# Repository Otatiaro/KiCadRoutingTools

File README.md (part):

# KiCad Routing Tools

A fast Rust-accelerated A* autorouter for KiCad PCB files. Compatible with **KiCad 9 and KiCad 10**. Available as both a **KiCad Plugin** with full GUI and a **Command-Line Interface** for scripting and automation.

📊 **[Project metrics](https://drandyhaas.github.io/KiCadRoutingTools/metrics/)** — installs, downloads and traffic, updated daily.

<p align="center">
  
  <br>
  Free and MIT-licensed. Donations cover the ~$500/month of cloud compute and AI development behind it.
  <br>
  Also via <a href="https://github.com/sponsors/drandyhaas">GitHub Sponsors</a> or <a href="https://www.paypal.me/DrAndyHaas">PayPal</a> — see <a href="#support">Support</a>.
</p>

## Contents

- [Support](#support) — donate via Ko-fi, GitHub Sponsors or PayPal
- [Features](#features)
- [Quick Start](#quick-start)
- [KiCad Plugin](#kicad-plugin) — GUI, the **AI Drive** tab (routing and placement), installation
- [Command-Line Interface](#command-line-interface) — routing, planes, verification
- [Documentation](#documentation) — full guide for every feature
- [Project Structure](#project-structure) & [Module Overview](#module-overview)
- [Performance](#performance)
- [Command Reference](#command-reference) — options per tool (full list: `--help` / [configuration.md](docs/configuration.md))
- [Project metrics](https://drandyhaas.github.io/KiCadRoutingTools/metrics/) — installs, downloads and traffic
- [Requirements](#requirements) · [Limitations](#limitations) · [Contributing](#contributing) · [License](#license)

## Support

KiCadRoutingTools is free and MIT-licensed, and it stays that way — there is no
paid tier, no feature held back, and nothing in this repository is paywalled.

Donations go to what it costs to build and maintain it: about **$500/month** of
cloud computing and AI-assisted development.

The compute is not incidental. Every change to the router is A/B-tested by
replaying a corpus of real open-source boards on rented cores and grading each
one for DRC violations and unconnected nets, and the ~770-file test suite fans
out the same way. It is what stops a change that helps one board from quietly
breaking ten others.

- **[☕ Donate on Ko-fi](https://ko-fi.com/drandyhaas)** — card or PayPal, no account needed.
- **[GitHub Sponsors](https://github.com/sponsors/drandyhaas)** — one-time or monthly, billed with any other projects you sponsor.
- Prefer PayPal directly? **[paypal.me/DrAndyHaas](https://www.paypal.me/DrAndyHaas)** (the sender needs a PayPal account).

A donation buys no priority support and unlocks no features. If you would rather
contribute something worth more than money, route one of your own boards and file
an issue for whatever breaks — see [Contributing](#contributing).

## Features

Fast, grid-based A\* routing with a native Rust core (~10× faster than pure Python): octilinear (H/V/45°) multi-layer routing with automatic vias, and batch routing with incremental obstacle caching. Highlights below link to the full deep-dive docs.

**Core routing**
- Rust-accelerated A\* pathfinding, multi-layer with automatic via insertion
- [Rip-up and reroute](docs/rip-up-reroute.md) — progressive N+1 blocker analysis, ripped-corridor avoidance
- [Net ordering strategies](docs/net-ordering.md) — MPS (crossing-aware), inside-out, original, or bus-first, with MPS layer swaps
- Stub layer switching, vertical track alignment, turn-cost straightening
- Board-edge (Edge.Cuts arcs/cutouts), keep-out rule areas, and auto BGA exclusion zones — see [Configuration](docs/configuration.md)
- Direction-aware stub / BGA / track [proximity penalties](docs/configuration.md)

**Differential pairs** — see [Differential Pairs](docs/differential-pairs.md)
- Pose-based A\* with a Dubins heuristic and adaptive setback angles for orientation-aware centerlines
- Bare-pad, multi-point (3+ terminals), and hybrid (coupled middle + single-ended legs) routing
- Automatic polarity resolution (opt-in pad swaps), U-turn prevention, GND return-via placement
- Electrically-short legs auto-defer to single-ended; per-layer [impedance-controlled](docs/differential-pairs.md) widths

**Power & planes** — see [Plane Routing](docs/route-plane.md) and [Power Nets](docs/power-nets.md)
- [Wider power-net routing](docs/power-nets.md) with automatic neck-down at fine-pitch pads
- Plane pours (pads are welded by the route step, #562) and plane layers several nets share (split round spines routed on the layer) with resistance / max-current reporting
- Disconnected-plane-region repair (region joins + pad taps) and GND return-via placement

**Signal integrity**
- [Length matching](docs/length-matching.md) — trombone meanders, auto DQ/DQS grouping, via-barrel aware
- [Time matching](docs/length-matching.md#time-matching) — propagation delay, microstrip vs stripline
- [Bus routing](docs/bus-routing.md), plus [guide corridors and keep-out zones](docs/configuration.md) drawn on a User layer

**Placement, fanout & optimization**
- [Placement by function](py_placer/placement/README.md): parts sorted into functional groups, one objective annealed (`place_simple.py`) over 12 seeds (6 started scattered, 6 with each group gathered), and a fast route (`route.py --quick 2`) of the 6 the objective rates best to keep the best (`/plan-pcb-placement`)
- [The design brief](docs/design-brief.md) — state what the board is FOR, in a sibling the toolchain reads: which connectors are user-facing, which edge each belongs on and where along it
- [Parts under other parts](docs/floorplan-intent.md#covers-and-heights-what-stands-over-the-board) — part heights read off the 3D models, so a low part may stand under a module or shield can where it fits; a card in its socket (M.2) or a module on a stacking connector is declared in the brief and moves with its connector, admitting only parts known to fit under it
- [Floorplan intent, graded](docs/floorplan-intent.md) — declare where parts belong and check the board against it, so "the render looks fine" stops being a verdict
- BGA / QFN fanout with decoupling-cap placement cleanup, Hungarian target-swap, and schematic sync

**Cleanup & verification** — see [Utilities](docs/utilities.md)
- Post-route copper cleanup reconciled against the connectivity model (no orphaned or ripped-and-not-restored copper), with gap-snap connectors
- **KiCad-oracle reconnect** — routes the exact links KiCad's own DRC reports as unconnected
- Checkers for DRC, connectivity, orphan stubs, copper hygiene (`check_weird.py`), and pad geometry

**Interfaces**
- Full [KiCad plugin GUI](#kicad-plugin) (KiCad 9 & 10) and a scriptable [CLI](#command-line-interface)
- [AI assistance](docs/claude-skills.md) — an **AI Drive** tab that plans an entire routing workflow or places a board by function, per-field "Ask AI" helpers, and datasheet-driven power / high-speed / diff-pair analysis
- [Board rendering](docs/utilities.md#board-renderer-route_renderpy) — fast geometry PNG renderer (`route_render.py`), placement stills (`render_placement.py`), a board's power components (`render_power.py`), and movies of a routing run (`route_movie.py`, made for every stress run) and of a placement, or the placement skill's whole flow through to the full route (`place_movie.py`)
- [Routing plans as files](docs/claude-skills.md#plans-from-the-command-line) — save/load a whole routing chain as JSON: build one from a recorded command chain (`make_plan.py`), run it headless through the real plugin (`run_plan.py`), or load it in the GUI

## Quick Start

### 1. Get the Code

```bash
# Clone with git
git clone https://github.com/drandyhaas/KiCadRoutingTools.git
cd KiCadRoutingTools
```

Or [download the ZIP](https://github.com/drandyhaas/KiCadRoutingTools/archive/refs/heads/main.zip) and extract it.

Commands here use `python3`. On Windows, use `py -3` (or `python`) if `python3` is not found.

### 2. Install the Rust Router

```bash
python3 build_router.py
```

By default this downloads a prebuilt binary for your OS from the project's
[GitHub Releases](https://github.com/drandyhaas/KiCadRoutingTools/releases) —
**no Rust toolchain required**. Prebuilts are published for:

- Linux x86_64
- macOS arm64 (Apple Silicon)
- macOS x86_64 (Intel)
- Windows x86_64

If a prebuilt isn't available for your platform (e.g. Linux arm64) or the
download fails, the script falls back to building locally with cargo.

#### Building from source (optional)

If you'd rather build locally — or you're on a platform without a prebuilt —
install Rust from [rustup.rs](https://rustup.rs/):

```bash
# macOS / Linux
curl --proto '=https' --tlsv1.2 -sSf https://sh.rustup.rs | sh

# Windows: Download and run rustup-init.exe from https://rustup.rs/
```

After installation, restart your terminal or run `source ~/.cargo/env`, then:

```bash
python3 build_router.py --from-source     # build locally instead of downloading
python3 build_router.py --tag v0.15.0     # download a specific release
python3 build_router.py --clean           # remove all build artifacts
```

### 3. Choose Your Interface

**Option A: KiCad Plugin (Recommended for interactive use)**

```bash
# Install the plugin
python3 install_plugin.py

# Then in KiCad: Tools → External Plugins → KiCadRoutingTools
```

**Option B: Claude Code (AI-assisted routing)**

Use [Claude Code](https://claude.ai/claude-code) to analyze your PCB and generate a routing plan:

```
> /plan-pcb-routing kicad_files/my_board.kicad_pcb
```

Claude will:
- Analyze your board structure and identify components needing fanout (BGA/QFN/PGA)
- Detect differential pairs and DDR signals requiring length matching
- Identify power/ground nets and recommend plane vs trace routing
- Assess signal speeds and recommend GND return via placement
- Generate a step-by-step routing plan with explanations
- Run the commands and verify results

Other useful skills:
```
> /find-high-speed-nets kicad_files/my_board.kicad_pcb       # Identify high-speed nets via datasheet lookup
> /analyze-power-nets kicad_files/my_board.kicad_pcb         # Identify power nets and track widths
> /identify-diff-pairs kicad_files/my_board.kicad_pcb        # Find diff pairs by pin function, recommend gap/impedance
> /recommend-stackup kicad_files/my_board.kicad_pcb          # Stackup advice for impedance/time-matching accuracy
> /recommend-plane-mappings kicad_files/my_board.kicad_pcb   # Which nets get planes, on which layers
> /diagnose-routing-failures my_board.kicad_pcb /tmp/route_output.txt  # Root-cause failed routes, get a retry command
> /review-routed-board my_board_routed.kicad_pcb             # Post-route QA: DRC, connectivity, length match, GND vias
> /plan-pcb-placement full kicad_files/my_board.kicad_pcb    # Group, place 12 seeds, fast-route the 6 cheapest, keep the best, route end to end
```

See [Claude Skills](docs/claude-skills.md) for what each skill does and how they fit together.

All of these are also available inside KiCad without leaving the plugin - see [AI assistance in the plugin](#ai-assistance-ai-drive-tab) below. The plugin can run the analysis and routing skills through [opencode](https://opencode.ai) instead of Claude Code (issue #503) - a Backend dropdown on the AI Drive tab selects the agent CLI, and opencode's `provider/model` strings open the door to other model providers. The placement runs need Claude Code, because they write files and opencode's analysis agent may not. The skills' output contracts are tuned on Claude models; smaller models may follow them less reliably.

**Option C: Manual Command Line (For scripting and automation)**

```bash
# Optionally place the board first, by its functional groups (see py_placer/placement/README.md)
python3 py_placer/place_simple.py my_board.kicad_pcb placed.kicad_pcb --groups groups.json --intent intent.json

# Pour the planes FIRST (#562): the fanout's plane-drop vias then land on
# real fill, and the route step welds plane pads into it.
python3 py_router/route_planes.py my_board.kicad_pcb poured.kicad_pcb --nets GND --plane-layers B.Cu

# Fan out a BGA, then tidy decoupling caps off the new vias (issue #130)
python3 py_router/bga_fanout.py poured.kicad_pcb -c U1 -o fanned.kicad_pcb --clearance 0.1
python3 py_placer/place_fanout_clearance.py fanned.kicad_pcb capclean.kicad_pcb --clearance 0.1

# Route differential pairs (the output is positional: route_diff's -o is --ordering)
python3 py_router/route_diff.py capclean.kicad_pcb diffed.kicad_pcb --nets "*lvds*"

# Route ALL remaining nets, plane nets included (their widths via --power-nets).
# This step ends with the in-run plane finalize that completes the planes.
python3 py_router/route.py diffed.kicad_pcb routed.kicad_pcb --nets "*" \
    --power-nets GND --power-nets-widths 0.3
```

---

## KiCad Plugin

The plugin provides a full graphical interface for all routing features, running directly within KiCad 9 or 10.

### AI assistance (AI Drive tab)

With [Claude Code](https://claude.ai/claude-code) or [opencode](https://opencode.ai) installed, the routing dialog gains AI assistance throughout (the plugin spawns the selected agent CLI headless, streams a live transcript, and fills GUI controls from the results). The **Backend** dropdown on the AI Drive tab picks the CLI: Claude Code runs Anthropic models; opencode takes `provider/model` strings for many providers (including its built-in free tier), with `opencode auth login` adding provider accounts. Both discover the same `.claude/skills/`; opencode runs them under a read-only `pcb-analysis` agent defined in `opencode.json` (the equivalent of the Claude run's read-only tool allowlist). Neither grants a dedicated write tool, though both grant `Bash`, so neither is a sandbox — the allowlist states intent, and `--allowedTools` auto-approves rather than restricts. Both can dispatch a subagent, so an analysis skill can hand its close-out to an independent verifier (#552): the Claude allowlist grants the dispatch tool per run, and the `pcb-analysis` agent grants opencode's `task` tool in `opencode.json`. A caller asking opencode for a tool set naming `Write`/`Edit` is refused rather than silently downgraded.

The tab has two sub-tabs:

- **Routing** - *Plan Routing* runs `/plan-pcb-routing`: the plan fills the parameter fields across the tabs and appears as a checkable step list, which *Run Selected Steps* executes sequentially in-process on the live board with per-step status marks. *Review Routed Board* and *Diagnose Routing Failures* give post-route QA and failure root-causing. Backend, model, and effort selectors control every AI run and persist with the dialog settings (model/effort remembered per backend).
- **Placement** - *Place (AI)* and *Place + Route (AI)* run `/plan-pcb-placement place` / `full` headless into a `krt_placement/` folder beside the board. The tab shows the seed candidates with a preview, a status line read from the run's milestone ledger, and at the end REPORT.md; *Apply Result to Board* moves the open board's parts to the result's poses and locks (and, after *Place + Route*, its routed copper). These two need Claude Code. *Beautify Labels* (no AI) tidies the reference-designator silkscreen (`py_placer/beautify_labels.py`).
- **Save / Load a plan** - *Save…* writes the generated step list to a JSON file; *Load…* reads one back and runs it with **no Claude call** — handy for replaying a workflow that worked on another board. A recorded command chain converts to a loadable plan too (`python3 py_router/make_plan.py <run dir>`; see [Plans from the command line](docs/claude-skills.md#plans-from-the-command-line)).
- **Per-field "Ask AI" buttons** - power nets/widths (Route tab), stackup check (Layers), differential-pair verification by pin function (Differential tab), net-to-plane layer mappings and GND return via distance (Planes tab).

The full button-to-skill map is in [Claude Skills - Plugin GUI Integration](docs/claude-skills.md#plugin-gui-integration). Datasheet-based skills use web lookups and take a few minutes; every run shows a live transcript with cancel.

### Installation

Three ways to install:

**A. KiCad Plugin and Content Manager (PCM)** — the recommended path for end users, and it needs no extra repository URL: the package has been in the **official KiCad repository** (the one KiCad ships with, `gitlab.com/kicad/addons`) since v0.15.6. Open the PCM from the KiCad main window, leave the repository dropdown on *KiCad official repository*, go to the **Plugins** tab, search for `routing`, select *KiCad Routing Tools* and click **Install**, then **Apply Changes** at the bottom. If it is not listed, the PCM is serving a cached catalogue — press **Refresh** and look again. Versions are published with status `testing` rather than `stable`, which the PCM shows in the Status column but does not hide or block; `kicad_version` is a *minimum*, so the 9.0 entry installs on KiCad 10 as well. On first launch, the plugin checks the Python packages listed in `requirements.txt` (`numpy`, `scipy`, `shapely`, and the optional `Pillow`, without which only board renders and the placement preview are off) and offers a one-click pip install for any that are missing **or too old** into KiCad's Python. Do not assume KiCad supplies them: what it bundles varies by version and platform, and KiCad 10 on macOS ships no `numpy` at all. The check reports the version and the file path the *running* interpreter imports — KiCad's Python is often not the one `pip show numpy` answers for in a terminal.

**B. PCM "Install from File…" using the release zip** — for a release newer than the one the official catalogue currently carries, for a pinned older version, or for an offline machine. Each [GitHub Release](https://github.com/drandyhaas/KiCadRoutingTools/releases) ships a ready-to-install PCM package zip named `KiCadRoutingTools-<version>.zip` (a single cross-platform archive bundling the prebuilt Rust binaries for all platforms — **not** the auto-generated "Source code (zip)"). To install it:

1. From the Release's *Assets*, download `KiCadRoutingTools-<version>.zip` (e.g. `KiCadRoutingTools-0.15.13.zip`).
2. In KiCad, open **Plugin and Content Manager** from the main window.
3. Click **Install from File…** (bottom of the PCM dialog) and select the downloaded zip.
4. Click **Apply Pending Changes**, then restart KiCad if prompted.

The plugin appears under *Tools → External Plugins* in the PCB Editor. The same first-launch `scipy`/`shapely` dependency check described in (A) applies. This path keeps the plugin manageable from the PCM (you can update or uninstall it there), unlike the manual install below.

**C. Manual install from source** — for development or for using the CLI tools as well:

```bash
# Install the plugin (copies to KiCad plugins directory)
python3 install_plugin.py

# For development: create symlink instead of copying
python3 install_plugin.py --symlink

# Remove the plugin
python3 install_plugin.py --uninstall

# Skip installing the Python dependencies
python3 install_plugin.py --no-deps
```

The installer installs into every KiCad version it finds (version directories and install roots are discovered, not taken from a fixed list), under:
- **macOS**: `~/Documents/KiCad/<version>/3rdparty/plugins/`
- **Linux**: `~/.local/share/kicad/<version>/3rdparty/plugins/`
- **Windows**: `~/Documents/KiCad/<version>/3rdparty/plugins/`

The installer also installs `requirements.txt` into KiCad's Python with pip, and skips pip when that Python already has everything. On Linux, KiCad runs the system Python, which Debian 12+, Ubuntu 23.04+, Fedora 38+ and Arch mark as externally managed (PEP 668) so pip refuses to install into it; there the installer runs no pip and prints the `apt` / `dnf` / `pacman` command for whatever is missing, plus the explicit `--break-system-packages` override for a package your distribution does not carry.

If you previously installed this plugin through the Plugin & Content Manager, that copy sits next to the local install and would shadow it on `sys.path` (causing stale-code errors). The installer detects any such PCM copy and moves it aside to `<kicad-base>/disabled_pcm_plugins/<version>/`, leaving it recoverable. Pass `--keep-pcm` to skip this.

### Releasing a new version (maintainers)

The full release flow — version bump, GitHub Release, and the merge request to the official KiCad PCM repository — is documented step by step in **[docs/release-pipeline.md](docs/release-pipeline.md)**.

Short version:

1. Bump `VERSION` and the `versions[]` entry in `metadata.json` (and `rust_router/Cargo.toml` only when the Rust crate changed); `python3 check_release_version.py --tag vX.Y.Z` checks they agree.
2. `git tag v0.15.6 && git push --tags` — CI builds all 4 platform binaries, packages a single `KiCadRoutingTools-<ver>.zip` (the PCM validator rejects duplicate version strings, so we ship one cross-platform zip), patches `metadata.json` with real sha256/size values, and attaches everything to the GitHub Release.
3. Append the new version to the metadata file in your fork of `gitlab.com/kicad/addons/metadata` and open an MR. See the docs page for the exact commands.

To build a zip locally for testing:

```bash
python3 package_pcm.py --binary-dir ./path/to/release/artifacts
```

### Usage

1. Open KiCad (9.0 or later)
2. Open a PCB in Pcbnew
3. *(Optional)* Select one or more nets in the PCB editor first — for example by
   clicking tracks/pads, or right-clicking a track and choosing
   **Select → All Tracks in Net**. Any nets you have selected are automatically
   pre-checked for routing when the plugin opens.
4. Go to **Tools → External Plugins → KiCadRoutingTools**
5. Configure routing parameters and select (or adjust) the nets to route
6. Click **Route** to run the router

### Plugin Tabs

**Route Tab:**
- Net selection with filtering and component filtering
- Nets selected in the PCB editor before opening the plugin are pre-checked automatically (also applies to the Fanout, Planes, and Differential tabs)
- Option to separate nets by net class (organizes into tabs per class)
- Track width, clearance, via size/drill from net class or manual override; impedance; the fab tier, escalation policy and clearance ceiling (the CLI's `--fab-tier`, `--escalation`, `--clearance-ceiling`)
- Layer selection with per-layer cost multipliers
- Options: stub layer swaps, copper text moving, teardrops, DRC-settings fix, power net widths and neck-down, no-BGA zones, smoothing
- **Guide corridor** - draw a polyline on a User layer (e.g. `User.1`) and tick "Follow User-layer guide path" to route the selected nets along it (waypoints, avoiding obstacles, packed non-overlapping)
- **Keepout zones** - draw one or more closed polygons on a User layer (e.g. `User.2`) and tick "Keep out of User-layer polygon(s)" to keep routed tracks out of those areas (hard keepout, all routed nets)
- **Clear guide/keepout layers** - optional "Clear guide layer after routing" / "Clear keepout layer after routing" checkboxes (unchecked by default) delete the drawn guide/keepout graphics from their User layer after a successful route, so you can draw fresh ones for the next run

**Advanced options Tab:**
- Swappable nets configuration for target swap optimization
- Routing parameters: iterations, heuristic weight, rip-up, probe iterations
- MPS ordering options, direction control, length matching
- Proximity settings: BGA, stub, track, via proximity costs
- Debug options

**Differential Tab:**
- Differential pair selection with filtering
- Pair width and gap, differential impedance, turning radius, setback angle configuration
- Options: polarity fix, GND vias, intra-pair length matching, AC-coupled end-to-end matching
- **Ask AI** confirms pairs by pin function

**Fanout Tab:**
- BGA fanout with exit margin, escape direction, differential pair support, and plane-net ball drops
- Escape method: auto (channel router, under-pad retry), channel, under-pad for dense fully-populated BGAs (issue #122), or dog-bone — see [BGA Fanout](py_router/bga_fanout/README.md#escape-methods)
- "Optimize decoupling cap placement" option (off by default) — after fanout, nudges decoupling caps off foreign-net fanout vias and toward same-net balls — see [Decap Clearance Repair](docs/utilities.md#decap-clearance-repair-place_fanout_clearancepy)
- QFN fanout with extension length, escape layer, and an under-pad (via-drop) escape
- Net selection for fanout operations

**Planes Tab** (pour creation only since #562 — plane repair runs inside
every route, and the route step welds plane pads into the pour):
- Net-to-layer assignment for power/ground planes (**Ask AI** recommends one)
- Create the pours (plus thermal via arrays under exposed pads, optional thermal-relief connections)
- Area via stitching, a board-edge via fence, and GND return via placement near signal vias
- Via size/drill, zone clearance configuration

**AI Drive Tab** — see [AI assistance](#ai-assistance-ai-drive-tab) above:
- *Routing* sub-tab: plan a routing chain with `/plan-pcb-routing` and run its steps; review and diagnose; save/load plans
- *Placement* sub-tab: place (and route) the board with `/plan-pcb-placement`; Beautify Labels

**Log Tab:**
- Real-time routing output display
- Color-coded messages (errors, warnings, success)

**About Tab:**
- Version information and credits
- Window transparency, *Validate PCB Data* (the pcbnew-built board model against the file parser's, reported in the Log tab) and *Reset All Settings to Defaults*

**General Features:**
- Settings persistence (parameters and selections preserved between sessions)
- Cancel button to stop routing operations mid-progress
- Results applied directly to the open PCB in KiCad

---

## Command-Line Interface

### Net Pattern Syntax

All `--nets` options support fnmatch-style wildcards and exclusion patterns:

| Pattern | Description |
|---------|-------------|
| `*` | All nets |
| `*DATA*` | Nets containing "DATA" |
| `/*` | Nets starting with "/" (hierarchical) |
| `Net-(U1-*)` | Nets matching "Net-(U1-...)" |
| `!GND` | Exclude net named "GND" |
| `!*VCC*` | Exclude nets containing "VCC" |
| `"*" "!GND" "!VCC"` | All nets except GND and VCC |

**Notes:**
- Exclusion patterns (starting with `!`) remove matching nets from the result
- Order matters: include patterns add nets, exclude patterns remove them
- Nets starting with "unconnected-" are automatically excluded
- Use quotes around patterns with special characters

### Route Nets

```bash
# Route all nets (default) - outputs to input_routed.kicad_pcb
python3 py_router/route.py kicad_files/input.kicad_pcb

# Route all nets, overwrite input file
python3 py_router/route.py kicad_files/input.kicad_pcb --overwrite

# Route all nets to a specific output file
python3 py_router/route.py kicad_files/input.kicad_pcb kicad_files/output.kicad_pcb

# Route specific nets (using --nets option)
python3 py_router/route.py kicad_files/input.kicad_pcb kicad_files/output.kicad_pcb --nets "Net-(U2A-DATA_0)" "Net-(U2A-DATA_1)"

# Route with wildcard patterns
python3 py_router/route.py kicad_files/input.kicad_pcb kicad_files/output.kicad_pcb --nets "Net-(U2A-DATA_*)"

# Route all nets on a component (auto-excludes GND/VCC/VDD/unconnected)
python3 py_router/route.py kicad_files/input.kicad_pcb kicad_files/output.kicad_pcb --component U1

# Route specific patterns on a component (no auto-exclusion)
python3 py_router/route.py kicad_files/input.kicad_pcb kicad_files/output.kicad_pcb --nets "/DDAT*" --component U1

# Route ALL nets on a component including power (use "*" pattern)
python3 py_router/route.py kicad_files/input.kicad_pcb kicad_files/output.kicad_pcb --nets "*" --component U1

# Exclusion-pattern SYNTAX demo (! prefix). NOTE: in the #562 chain you do
# NOT exclude plane nets from the route step -- see the chain example below.
python3 py_router/route.py kicad_files/input.kicad_pcb kicad_files/output.kicad_pcb --nets "*" "!GND" "!VCC"

# Route one placement BLOCK -- a schematic sheet, a KiCad group, a net-name prefix, an IC and
# its decaps (--group-by kicad,sheet,netprefix,decap; auto = kicad,sheet; --list-groups shows them)
python3 py_router/route.py kicad_files/input.kicad_pcb kicad_files/output.kicad_pcb \
  --group-by sheet --list-groups                      # what blocks exist?
python3 py_router/route.py kicad_files/input.kicad_pcb kicad_files/output.kicad_pcb \
  --group sheet:558c3023 --group-by sheet --group-scope internal

# PREVIEW any routing run: route it, report what it WOULD add, write no board
python3 py_router/route.py kicad_files/input.kicad_pcb kicad_files/output.kicad_pcb \
  --group sheet:558c3023 --group-by sheet --preview --preview-png preview.png

# UNDO: strip the scoped nets' copper back to unrouted (needs an explicit scope;
# defaults to --group-scope internal, since a block's "touching" nets include
# GND/VCC and undoing those would strip their copper across the whole board)
python3 py_router/route.py kicad_files/input.kicad_pcb kicad_files/undone.kicad_pcb \
  --group sheet:558c3023 --group-by sheet --undo

# Route differential pairs (use route_diff.py)
python3 py_router/route_diff.py kicad_files/input.kicad_pcb kicad_files/output.kicad_pcb --nets "*lvds*" --no-bga-zones

# Route with wider tracks for power nets
python3 py_router/route.py kicad_files/input.kicad_pcb kicad_files/output.kicad_pcb --nets "Net*" \
  --power-nets "*GND*" "*VCC*" "+3.3V" --power-nets-widths 0.4 0.5 0.3 --track-width 0.2

# Typical workflow: create GND plane first, then route all signals
python3 py_router/route_planes.py kicad_files/flat_hierarchy.kicad_pcb --nets GND --plane-layers B.Cu
python3 py_router/route.py kicad_files/flat_hierarchy_routed.kicad_pcb --overwrite

# No agent: build the whole chain (planes, fanouts, decaps, diff pairs, route)
# from the board's own rules and footprints, and run it; --dry-run prints the plan
python3 py_router/autoplan.py kicad_files/input.kicad_pcb kicad_files/output.kicad_pcb
python3 py_router/autoplan.py kicad_files/input.kicad_pcb kicad_files/output.kicad_pcb --dry-run
```

### Create Power/Ground Planes

```bash
# Pour a GND zone on B.Cu (outputs to input_routed.kicad_pcb). The pour places no
# per-pad taps: the route step that follows welds the plane pads into it (#562)
python3 py_router/route_planes.py kicad_files/input.kicad_pcb --nets GND --plane-layers B.Cu

# Create GND zone, overwrite input file
python3 py_router/route_planes.py kicad_files/input.kicad_pcb --overwrite --nets GND --plane-layers B.Cu

# Create GND zone to specific output file
python3 py_router/route_planes.py kicad_files/input.kicad_pcb kicad_files/output.kicad_pcb --nets GND --plane-layers B.Cu

# Create multiple planes at once (each net paired with corresponding plane layer)
python3 py_router/route_planes.py kicad_files/input.kicad_pcb --nets GND +3.3V --plane-layers In1.Cu In2.Cu

# VCC plane; --via-size/--via-drill size this step's own vias (thermal arrays, stitching)
python3 py_router/route_planes.py kicad_files/input.kicad_pcb --nets VCC --plane-layers In2.Cu --via-size 0.5 --via-drill 0.4

# Multiple nets sharing one layer, split round spines routed on it (use | separator)
python3 py_router/route_planes.py kicad_files/input.kicad_pcb --nets GND "VA19|VA11" --plane-layers In4.Cu In5.Cu

# Dry run to see what would be placed
python3 py_router/route_planes.py kicad_files/input.kicad_pcb --nets GND --plane-layers B.Cu --dry-run
```

GND return vias (`--add-gnd-vias`) and area stitching (`--stitch-vias`, `--stitch-edge-fence`) go in a re-run of the same pour after routing, so they place around the finished signals — see [Plane Routing](docs/route-plane.md).

### Repair Disconnected Plane Regions

> **Since #562 you normally do not run this step.** Every `route.py` run
> finishes with an in-run *plane finalize* that applies this same engine
> (pad taps + region joins), the plane-copper cleanup, and a KiCad-oracle
> completion check — so a pours-first chain repairs its planes automatically.
> `KICAD_PLANE_FINALIZE=0` is the kill switch. The finalize runs even when
> the route step finds nothing else to route (#1112), so a chain should end
> on `route.py`, never on this script. Use the standalone script below for a
> board routed OUTSIDE that chain (e.g. hand-edited copper); its track and
> via default to the board's Default net class, not to the sizes a chain
> routed at, so pass `--track-width` / `--via-size` / `--via-drill` if they
> differ.

After creating power planes, regions may become split by vias and traces from other nets. Use `repair_planes.py` to reconnect them:

```bash
# Auto-detect all zones in PCB and repair disconnected regions (outputs to input_routed.kicad_pcb)
python3 py_router/repair_planes.py kicad_files/input.kicad_pcb

# Auto-detect all zones, overwrite input
python3 py_router/repair_planes.py kicad_files/input.kicad_pcb --overwrite

# Auto-detect all zones to specific output file
python3 py_router/repair_planes.py kicad_files/input.kicad_pcb kicad_files/output.kicad_pcb

# Specific nets and layers
python3 py_router/repair_planes.py kicad_files/input.kicad_pcb --nets GND --plane-layers B.Cu

# Customize track width and clearance
python3 py_router/repair_planes.py kicad_files/input.kicad_pcb kicad_files/output.kicad_pcb \
    --track-width 0.5 --clearance 0.2
```

### Review a Placement

Placement deltas are invisible in a board file; render them instead.

```bash
# what moved, and did it help? (ghosts at the seed poses, arrows, metrics caption)
python3 py_tools/render_placement.py placed.kicad_pcb --before seed.kicad_pcb -o delta.png

# zoom to one placement block; same block names as route.py --group
python3 py_tools/render_placement.py board.kicad_pcb --list-groups --group-by sheet
python3 py_tools/render_placement.py board.kicad_pcb --zoom-group sheet:58d913ec --per-side -o out/

# everything a placement author reads, in one artifact: escape lanes, groups, and
# lock advice (which parts should NOT move) -- locks nothing, writes no board
python3 py_tools/board_brief.py board.kicad_pcb
```

Toggles for `--borders` / `--labels` / `--ratsnest` / `--arrows` / `--ghosts`;
`--per-side` gives F and B panels rather than one flattened projection.
The render is triage, and so are the caption's `crossings` / `hpwl`: a
placement is judged by routing it.

### Verify Results

```bash
# Check for DRC violations. With no -c, grades at the Default net-class clearance
# the routing steps wrote into the sibling .kicad_pro (the clearance the board was
# routed to), plus the board's .kicad_dru layer rules; falls back to 0.2mm if
# there's no project. Pass -c to override.
python3 py_router/check_drc.py kicad_files/output.kicad_pcb

# Cross-check with KiCad's own DRC engine (requires KiCad; --refill-zones avoids
# bogus zone-clearance errors from stale pours - see tests/README.md for details)
kicad-cli pcb drc --refill-zones --format json -o drc.json kicad_files/output.kicad_pcb

# ...because a routed board ships zone OUTLINES with no filled_polygon, so an
# unrefilled grade reports plane opens that are not real (#910). To ship a
# board that already carries its fills, add --write-fill to the route step, or:
python3 py_tools/fill_for_delivery.py kicad_files/output.kicad_pcb -o delivered.kicad_pcb

# Check connectivity (detects unrouted nets, broken routes, and T-junctions)
python3 py_router/check_connected.py kicad_files/output.kicad_pcb

# Check connectivity for specific nets
python3 py_router/check_connected.py kicad_files/output.kicad_pcb --nets "*DATA*"

# Check connectivity for all nets on a component
python3 py_router/check_connected.py kicad_files/output.kicad_pcb --component U1

# Only check routed nets (skip unrouted net detection)
python3 py_router/check_connected.py kicad_files/output.kicad_pcb --routed-only

# Check for orphan stubs (dead-end traces with no pad/via/trace at the loose end).
# Connection is judged by actual copper extent (via radius, pad size, trace
# half-width), so T-junction taps and copper-overlap joints are not miscounted.
python3 py_tools/check_orphan_stubs.py kicad_files/output.kicad_pcb

# Other-net copper inside the screw-head ring of each mounting hole (KiCad checks
# a hole's clearance only). Declare the ring before routing with
# add_rule_area.py --name MOUNT --mounting-holes. --ring MM sets how far past the
# hole edge the head reaches (default 0.4 x the drill).
python3 py_tools/check_mounting_holes.py kicad_files/output.kicad_pcb --ring 1.3

# Pad-geometry sanity check: flags same-footprint, different-net pads whose copper
# overlaps (a short). A non-zero result almost always means a pad's rotation/size
# is modelled wrong - the usual cause is a QFN/QFP/BGA placed at a non-orthogonal
# angle. The fanout tools run this automatically on their component first; run it
# yourself before fanout (or board-wide) as a standalone check:
python3 py_router/check_pads.py kicad_files/board.kicad_pcb                 # whole board, per footprint
python3 py_router/check_pads.py kicad_files/board.kicad_pcb --component U23 # one footprint
python3 py_router/check_pads.py kicad_files/board.kicad_pcb --cross-footprint  # also across parts

# Flag long non-orthonormal tracks. An on-grid router emits only 0/45/90-degree
# segments; the only legitimate non-orthonormal segment is a short (<=1 grid cell)
# terminal connector to an off-grid pad/ball. Anything longer is a routing defect
# (it can cut diagonally across foreign copper). qfn_fanout escape stubs are
# excluded automatically; bga_fanout's short stub-end jogs clear the 0.25mm default.
python3 py_tools/check_orthonormal.py kicad_files/output.kicad_pcb

# Copper hygiene (read-only): dangling stubs, same-net soft joints, redundant
# cycles, and removable / stacked / floating copper the routing left behind.
python3 py_router/check_weird.py kicad_files/output.kicad_pcb

# Is the board DONE? One verdict over board_score and the checkers above, which
# fails closed: exit 0 done, 4 incomplete, 5 graded clean only against floors
# the routing lowered (--authored-from names the board the chain started from)
python3 check_complete.py kicad_files/output.kicad_pcb --authored-from kicad_files/input.kicad_pcb
```

See [Utilities](docs/utilities.md) for every checker and its options, and
`python3 krt_registry.py` for every runnable tool in the clone with its purpose.

### Power Net Analysis

Use the `/analyze-power-nets` skill to identify power nets and get track width recommendations:

```
# Ask the AI to analyze your board with datasheet lookup
/analyze-power-nets kicad_files/my_board.kicad_pcb
```

The skill:
1. Auto-classifies obvious components (resistors, capacitors, inductors, etc.)
2. Uses WebSearch to look up datasheets for unknown components (ICs, connectors, transistors)
3. Classifies each component's role (power source, current sink, pass-through, shunt)
4. Traces power paths from sinks to sources
5. Generates ready-to-use `--power-nets` configurations

See [Power Net Analysis](docs/power-nets.md) for detailed documentation.

### High-Speed Net Analysis

Use the `/find-high-speed-nets` skill to identify high-speed nets and get GND return via recommendations:

```
# Ask the AI to analyze signal speeds with datasheet lookup
/find-high-speed-nets kicad_files/my_board.kicad_pcb
```

The skill:
1. Pre-classifies nets by name patterns (DDR, USB, SPI, CLK, etc.)
2. Pre-classifies components by footprint (FPGA, DDR, PHY, etc.)
3. Uses WebSearch to look up datasheets for ICs and extract max clock rates and rise times
4. Traces high-speed signals through series passives (termination resistors, AC coupling caps)
5. Generates a speed classification (ultra-high/high/medium/low) with recommended `--gnd-via-distance`

The `/plan-pcb-routing` skill includes a lightweight version of this analysis (net name and
footprint pattern matching only, no datasheet lookup) and automatically includes a GND return
via step when GND planes are present. Run `/find-high-speed-nets` first for more accurate
recommendations based on actual component specifications.

### Integration Tests

```bash
# Run full integration test (fanout + routing + checks)
python3 tests/test_fanout_and_route.py --all

# Quick mode for faster testing
python3 tests/test_fanout_and_route.py --all --quick

# The whole suite (~770 files, about 40 minutes on one machine when last measured)
python3 tests/run_all.py
```

See [tests/README.md](tests/README.md) for detailed documentation of all test scripts.

## Documentation

| Document | Description |
|----------|-------------|
| [Routing Architecture](docs/routing-architecture.md) | Module structure, obstacle maps, A* algorithm |
| [Python API](docs/python-api.md) | Using the modules as a library: parser, writer, modification, config, net analysis, impedance — with runnable examples |
| [Configuration](docs/configuration.md) | Command-line options, GridRouteConfig parameters |
| [Differential Pairs](docs/differential-pairs.md) | P/N pairing, polarity swaps, via handling |
| [Net Ordering](docs/net-ordering.md) | MPS algorithm, inside-out ordering, strategy comparison |
| [Rip-Up and Reroute](docs/rip-up-reroute.md) | Blocking analysis, progressive N+1 escalation, reroute loop |
| [Length Matching](docs/length-matching.md) | Trombone meanders, via barrel lengths, DDR auto-grouping, time matching |
| [Bus Routing](docs/bus-routing.md) | Bus detection and filter, corridor planning, middle-out ordering, corridor attraction; the topo bus step |
| [Guide Corridor](docs/configuration.md#guide-corridor-options-preferred-route) | User-layer guide paths, waypoints, best-effort following |
| [Power/Ground Planes](docs/route-plane.md) | Copper zones with automatic via placement |
| [Utilities](docs/utilities.md) | Every checker (DRC, connectivity, completion, hygiene, pads), the fanout generators, placement tools, renderers, the DRC-settings fixer |
| [Design Brief](docs/design-brief.md) | Declare what the board IS -- the facts a board file cannot contain -- and compile them into the intent (`<board>.design-brief.json`) |
| [Floorplan Intent](docs/floorplan-intent.md) | Declare the floorplan, grade the board against it (`check_floorplan.py`) |
| [BGA Fanout](py_router/bga_fanout/README.md) | BGA escape routing generator |
| [QFN Fanout](py_router/qfn_fanout/README.md) | QFN/QFP escape routing generator |
| [Rust Router](rust_router/README.md) | Building and using the Rust A* module |
| [Power Net Analysis](docs/power-nets.md) | Power net detection, AI analysis, track width guidelines |
| [Claude Skills](docs/claude-skills.md) | All ten AI skills: placement and routing end to end, routing plans, power/high-speed/diff-pair analysis, stackup, plane mappings, failure diagnosis, board review |
| [Placement](py_placer/placement/README.md) | Placement by function: groups, one annealed objective, legality, the floorplan intent's grade |
| [Integration Tests](tests/README.md) | Test scripts and performance benchmarks |
| [Release Pipeline](docs/release-pipeline.md) | How to tag a release and submit it to the KiCad PCM (maintainers) |

## Project Structure

```
KiCadRoutingTools/
├── py_router/                # Routing engine + CLI entry points (~130 modules)
│   ├── route.py                  # Main CLI - single-ended routing (ends with the in-run plane finalize, #562)
│   ├── route_diff.py             # Main CLI - differential pair routing
│   ├── route_planes.py           # Main CLI - power/ground plane pours
│   ├── repair_planes.py          # Standalone utility - repair disconnected plane regions (the chain step is absorbed into route.py's finalize, #562)
│   ├── route_render.py           # PNG still of a board from its geometry
│   ├── route_movie.py            # Movie of a routing run, step by step (route_trace.py records the router's events)
│   ├── make_plan.py              # Recorded command chain -> GUI routing plan (plan.json)
│   ├── run_plan.py               # Run a GUI routing plan headless, through the real plugin dialog
│   ├── autoplan.py               # Build a routing chain from the board itself and run it, no agent
│   ├── add_rule_area.py          # Write a copper keep-out rule area onto a board
│   ├── plane_io.py               # Plane I/O utilities (zone extraction, output writing)
│   ├── plane_obstacle_builder.py # Obstacle map building for plane via placement
│   ├── plane_blocker_detection.py # Blocker detection and rip-up for plane vias
│   ├── plane_zone_geometry.py    # Voronoi cells for a shared plane layer's split
│   ├── plane_split_raster.py     # Raster finishing of a shared plane layer's split
│   ├── plane_resistance.py       # Plane resistance and current capacity calculations
│   ├── plane_region_connector.py # Detect and route between disconnected plane regions
│   ├── routing_config.py         # GridRouteConfig, GridCoord, DiffPairNet classes
│   ├── routing_defaults.py       # Default routing parameter values
│   ├── routing_state.py          # RoutingState class - tracks routing progress
│   ├── routing_common.py         # Shared utilities for route.py and route_diff.py
│   ├── obstacle_map.py           # Obstacle map building functions
│   ├── obstacle_cache.py         # Net obstacle caching for incremental builds
│   ├── diff_pair_loop.py         # Differential pair routing loop
│   ├── single_ended_loop.py      # Single-ended routing loop
│   ├── reroute_loop.py           # Reroute queue processing
│   ├── diff_pair_routing.py      # Diff pair A* routing implementation
│   ├── single_ended_routing.py   # Single-ended A* routing implementation
│   ├── net_ordering.py           # MPS, inside-out, and original ordering
│   ├── rip_up_reroute.py         # Rip-up and reroute logic
│   ├── length_matching.py        # Length matching with trombone meanders
│   ├── kicad_parser.py           # KiCad .kicad_pcb file parser
│   ├── kicad_writer.py           # KiCad S-expression generator
│   ├── output_writer.py          # Route output and swap application
│   ├── pcb_modification.py       # Add/remove routes from PCB data
│   ├── impedance.py              # Impedance calculation (microstrip/stripline formulas)
│   ├── check_drc.py              # DRC violation checker
│   ├── check_connected.py        # Connectivity checker (with T-junction detection)
│   ├── check_pads.py             # Pad-geometry sanity checker
│   ├── check_weird.py            # Copper hygiene checker
│   ├── cleanup_pipeline.py       # The one ordered post-route cleanup pipeline (both routing fronts)
│   ├── fix_kicad_drc_settings.py # Make .kicad_pro DRC constraints consistent with the routed floors
│   ├── copy_board.py             # Copy a board WITH its sibling .kicad_pro/.kicad_dru
│   ├── list_nets.py              # List nets on a component
│   ├── startup_checks.py         # Startup checks (Python deps, Rust library version)
│   ├── bga_fanout.py             # BGA fanout CLI wrapper
│   ├── bga_fanout/               # BGA fanout package (escape, reroute, layer balance, under-pad escape, ...)
│   ├── qfn_fanout.py             # QFN/QFP fanout CLI wrapper
│   ├── qfn_fanout/               # QFN/QFP fanout package (layout, geometry, types)
│   └── ...                       # plus the rest of the engine modules — see Module Overview below
│
├── py_placer/                # Placement CLIs and the placement package
│   ├── place_simple.py           # The placer: functional groups, one objective, annealed
│   ├── place_movie.py            # place_simple with a camera: a movie of the placement, step by step
│   ├── judge_seeds.py            # The seed judge: judge.json's seeds routed by one quick chain, scored
│   ├── place_pose.py             # Set, turn, face, lock or replicate parts by hand
│   ├── place_fanout_clearance.py # Move decoupling caps off fanout vias
│   ├── beautify_labels.py        # Tidy the reference-designator silkscreen
│   ├── converge.py               # The milestone ledger: record, where, verdict
│   ├── placement/                # Component placement package — see py_placer/placement/README.md
│   │   ├── simple.py             # The placer's cost model
│   │   ├── simple_anneal.py      # The placer's simulated annealing
│   │   ├── quench.py             # QuenchState: the parts, their poses and the board
│   │   ├── grouping.py           # The groups file
│   │   ├── legality.py           # Placement legality checks
│   │   ├── floorplan.py          # Floorplan intent and its grade
│   │   ├── body.py               # THE footprint body model (#896)
│   │   ├── fanout_clearance.py   # Fanout clearance evaluation
│   │   ├── parser.py             # Courtyard boundary extraction
│   │   ├── writer.py             # Footprint position modification
│   │   └── ...
│   └── ...
│
├── py_tools/                 # Leaf diagnostic / analysis tools
│   ├── check_impedance.py        # Verify impedance-controlled widths/gaps
│   ├── check_orphan_stubs.py     # Orphan stub detector
│   ├── check_mounting_holes.py   # Other-net copper under a mounting hole's screw head
│   ├── check_cycles.py           # Redundant-loop (cycle) + overlapping-via checker
│   ├── check_orthonormal.py      # Long non-orthonormal track detector
│   ├── net_forensics.py          # Per-net copper forensics
│   ├── kicad_unconnected.py      # Unconnected-item listing
│   ├── validate_pcb_data.py      # PCBData validation
│   ├── extract_pcb_geometry.py   # Geometry extraction
│   ├── clean_ignored.py          # List / delete git-ignored files
│   ├── analyze_power_paths.py    # Power-path analysis (backs /analyze-power-nets)
│   ├── board_brief.py            # What a board looks like to whatever places it
│   ├── board_context.py          # Every part's value, pins, nets and role
│   ├── check_groups.py           # Check a groups file against its board
│   ├── check_floorplan.py        # Grade a board against its floorplan intent
│   ├── check_assembly.py         # Is a placement buildable?
│   ├── render_placement.py       # PNG stills of a placement, with its legality
│   ├── route_review.py           # What to move after a route
│   ├── render_nets.py            # Chosen nets' copper on several boards side by side
│   ├── render_power.py           # A board's power components over its rails
│   ├── board_score.py            # One score for a board: blocking, then quality
│   ├── quick_score.py            # Score a route.py --quick 2 board (the placement seed judge)
│   ├── check_reachability.py     # Is this pad reachable, or is the geometry to blame?
│   ├── check_join.py             # Verify a hand-drawn join against all board copper before committing it
│   ├── fill_for_delivery.py      # Write a filled copy of a routed board (#910)
│   └── _path.py                  # sys.path bootstrap so the tools import py_router
│
├── tests/                    # Tests (~770 files) and the stress/A-B harness
│   ├── run_all.py                # The whole suite (tests/stress/modal_suite/ fans it out onto Modal)
│   ├── test_fanout_and_route.py  # Full integration test (fanout + route)
│   ├── test_kit_route.py         # Pad-to-pad routing test (no fanout)
│   ├── test_flat_hierarchy.py    # 2-layer board with GND plane test
│   ├── test_interf_u.py          # 2-layer board with non-rectangular outline test
│   ├── test_sonde_u.py           # Wide track routing test
│   ├── run_utils.py              # Shared test utilities
│   ├── gui_parity/               # CLI/GUI parity gates — see tests/gui_parity/README.md
│   └── stress/                   # Real-world-board stress-test harness (run_queue.sh) — see tests/README.md
│
├── rust_router/              # Rust A* implementation
├── kicad_routing_plugin/     # KiCad ActionPlugin
│   ├── action_plugin.py      # ActionPlugin entry point
│   ├── swig_gui.py           # Main routing dialog (Route/Advanced options tabs)
│   ├── differential_gui.py   # Differential pair routing tab
│   ├── fanout_gui.py         # BGA/QFN fanout tab and net selection panel
│   ├── planes_gui.py         # Power/ground planes tab
│   ├── ai_gui.py             # AI Drive tab, Routing sub-tab (spawns the agent CLI headless, streams transcript)
│   ├── ai_plan.py            # Routing plans: parse, fill the tabs, run the steps (PlanExecutor)
│   ├── placement_gui.py      # AI Drive tab, Placement sub-tab (+ Beautify Labels)
│   ├── placement_run.py      # Placement run folders, prompts and progress (krt_placement/)
│   ├── ai_backend.py         # Agent CLI backend selection (Claude Code / opencode)
│   ├── board_swaps.py        # Shared board pad/net swap helpers
│   ├── deps_check.py         # Plugin dependency checks
│   ├── about_tab.py          # About tab with version info
│   ├── gui_utils.py          # Shared GUI utilities
│   └── settings_persistence.py  # Save/restore dialog settings between sessions
├── build_router.py           # Rust module build script (--clean to remove artifacts)
├── install_plugin.py         # Plugin installer script
├── check_complete.py         # Is this board DONE? One fail-closed verdict
├── krt_registry.py           # Every runnable tool in the clone, its purpose and kind
├── krt_capabilities.py       # What this clone can do, as JSON (also route.py --capabilities)
├── package_pcm.py            # Build the KiCad PCM zip (maintainers)
├── requirements.txt          # Python dependencies
├── kicad_files/              # Example and test boards
├── docs/                     # Documentation
└── .claude/skills/           # Claude Code skills
    ├── analyze-power-nets/   # AI-powered power net analysis skill
    ├── find-high-speed-nets/ # AI-powered high-speed net identification skill
    ├── plan-pcb-routing/     # AI-powered routing plan generation skill (orchestrates the others)
    ├── identify-diff-pairs/  # Datasheet-based diff pair detection skill
    ├── recommend-stackup/    # Stackup review/recommendation skill
    ├── recommend-plane-mappings/  # Net-to-plane-layer assignment skill
    ├── diagnose-routing-failures/  # Failure root-cause and retry skill
    ├── plan-pcb-placement/   # Place by function, fast-route seeds, keep the best, route; one verifier, report
    ├── review-routed-board/  # Post-route QA and sign-off skill
    └── stress-test-router/   # Batch stress-test on real-world boards + issue filing (dev/QA)
```

## Module Overview

One-line summaries below (all of these modules live in `py_router/`); the
[Python API documentation](docs/python-api.md) has full per-module references
(signatures, dataclass fields, gotchas) with runnable examples.

### Core Routing

| Module | Purpose |
|--------|---------|
| `route.py` | CLI for single-ended routing |
| `route_diff.py` | CLI for differential pair routing |
| `route_planes.py` | CLI for power/ground plane pours (#562 bare pour), thermal via arrays, stitching and GND return vias |
| `repair_planes.py` | CLI for repairing disconnected plane regions on a board routed outside the chain (route.py's in-run plane finalize runs the same engine) |
| `routing_config.py` | Configuration classes (`GridRouteConfig`, `GridCoord`, `DiffPairNet`) |
| `routing_defaults.py` | Every default routing parameter, in one place (`FAB_TIER`, `ESCALATION`, `CLEARANCE`, ...) |
| `design_rules.py` | KiCad design rules resolved in KiCad's own order (#530): pad overrides, net classes, `.kicad_dru` rules, Board Setup minimums |
| `kicad_dru.py` | Per-layer clearance rules from the board's `.kicad_dru` (#498) |
| `fab_tiers.py` | Fab-capability floors (`--fab-tier`) and the escalation policy (`--escalation`) |
| `routing_state.py` | `RoutingState` class tracking progress, results, and PCB modifications |
| `routing_context.py` | Helper functions for building obstacles and recording success |
| `routing_common.py` | Shared utilities for route.py and route_diff.py (BGA zones, net resolution, length matching) |
| `routing_utils.py` | Shared utilities (`build_layer_map`, `iter_pad_blocked_cells`) |
| `obstacle_map.py` | Obstacle map building from PCB data |
| `obstacle_cache.py` | Net obstacle caching for incremental obstacle map builds |
| `obstacle_costs.py` | Stub and track proximity cost calculations |
| `sense_branch.py` | Protected Kelvin sense branches (#1279), declared by a KiCad group named `sense:<REF>.<PAD>` (the join pad): the member copper and its sense pads are foreign to their own net except on the join pad, so new copper joins the branch only there |
| `net_keepouts.py` | Net-filtered copper keep-outs from the board's `.kicad_dru` (`disallow` rules on a named rule area): the regions, stamped into the obstacle map only while a net a rule binds routes, and the audit of bound-net copper the shipped board has inside one |
| `pad_entry.py` | Row-pad flanks: the long sides of a net's fine-pitch row pads, blocked while that net routes (route step and plane pad taps) and refused to the octolinear smoother and to a tap's via site, so a track lands on such a pad through an end, along its axis |
| `keep_away.py` | Pairwise keep-away between net groups (#1146): the per-net band cost and the in-band report; the design brief's `keep_away` rules, read for the router and the placement grade alike (#1253) |
| `bresenham_utils.py` | Bresenham line-walking utilities for grid-based segment operations |
| `geometry_utils.py` | Shared geometry calculations (point-to-segment distance, segment intersection, UnionFind) |
| `routing_constants.py` | Shared constants (default layer stack, power net patterns, tolerances) |
| `terminal_colors.py` | ANSI color codes for terminal output |

### Routing Loops

| Module | Purpose |
|--------|---------|
| `diff_pair_loop.py` | Main loop for routing differential pairs |
| `single_ended_loop.py` | Main loop for routing single-ended nets |
| `reroute_loop.py` | Processes reroute queue for failed routes |
| `phase3_routing.py` | Phase 3 multi-point tap routing (connects remaining pads after length matching) |
| `diff_pair_routing.py` | Differential pair A* with centerline + offset and GND vias |
| `diff_pair_multipoint.py` | Multi-point and hybrid (coupled middle + single-ended legs) differential pairs |
| `single_ended_routing.py` | Single-ended net A* routing |
| `group_routing.py` | Route, preview and undo one placement block (`route.py --group/--preview/--undo`) |

### Net Analysis

| Module | Purpose |
|--------|---------|
| `net_ordering.py` | MPS, inside-out, and original net ordering strategies |
| `net_queries.py` | Net queries (diff pair detection, MPS ordering, power net detection, chip pad positions) |
| `connectivity.py` | Stub endpoints, connected groups, multi-point net detection, MST edges |
| `bus_detection.py` / `bus_corridor.py` | Bus groups of nets with clustered endpoints, and one planned centerline per bus (`--bus`) |
| `diff_xnet.py` | AC-coupled differential pairs (XNets) through series caps (#196) |

Key functions in `net_queries.py`:
- `identify_power_nets(pcb, patterns, widths)` - Pattern-based power net detection for `--power-nets` CLI option
- `compute_mps_net_ordering(pcb, net_ids)` - MPS algorithm for optimal net ordering
- `find_differential_pairs(pcb, patterns)` - Detect P/N pairs from net names (suffix-style aware: `+`/`-` nets only pair with each other, never with `_P`/`_N` nets sharing the same base name)

Key functions in `py_tools/analyze_power_paths.py` (used by `/analyze-power-nets` skill):
- `analyze_pcb(filepath)` - Load PCB and extract components for analysis
- `get_components_needing_analysis(components)` - Get components requiring AI classification
- `classify_component(components, ref, role, current_rating_ma, notes, supply_nets)` - Set component classification (`supply_nets` names the rails of a part whose pads carry no pintype and whose nets are not rail-named)
- `trace_power_paths(pcb, components)` - Trace each load upstream (regulators entered output to input only) to the source feeding it
- `get_power_net_recommendations(pcb, components, paths)` - Get recommended track widths (a sink's rating is charged once per net; a source's rating is a limit, never a load)

### Optimization

| Module | Purpose |
|--------|---------|
| `layer_swap_optimization.py` | Upfront layer swap optimization before routing |
| `layer_swap_fallback.py` | Try layer swap when route fails |
| `stub_layer_switching.py` | Low-level stub layer swap utilities |
| `mps_layer_swap.py` | MPS-aware layer swap for crossing conflicts |
| `polarity_swap.py` | P/N polarity swap for differential pairs |
| `target_swap.py` | Hungarian algorithm for optimal target assignment |
| `rip_up_reroute.py` | Rip-up blocking routes and retry |
| `blocking_analysis.py` | Analyze which nets are blocking |
| `length_matching.py` | Length matching with trombone-style meanders |

### Recovery, Planes and Post-Route

| Module | Purpose |
|--------|---------|
| `net_rescue.py` | Last-chance scoped retry of failed nets at finer parameters, then the terminal geometry escalation |
| `plane_pad_tap.py` / `plane_region_connector.py` | Plane pad taps and region joins: the engine of route.py's in-run plane finalize and of `repair_planes.py` |
| `kicad_oracle.py` | KiCad-oracle reconnect: routes the exact links KiCad's own connectivity reports open |
| `cleanup_pipeline.py` | The one ordered post-route cleanup pipeline both routing fronts run |
| `improvement_gate.py` | Never ship a board a run made worse (#600): reverts the step when connectivity regressed |
| `fix_kicad_drc_settings.py` | Write the routed floors into the output's `.kicad_pro` so KiCad's DRC grades what was routed |
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
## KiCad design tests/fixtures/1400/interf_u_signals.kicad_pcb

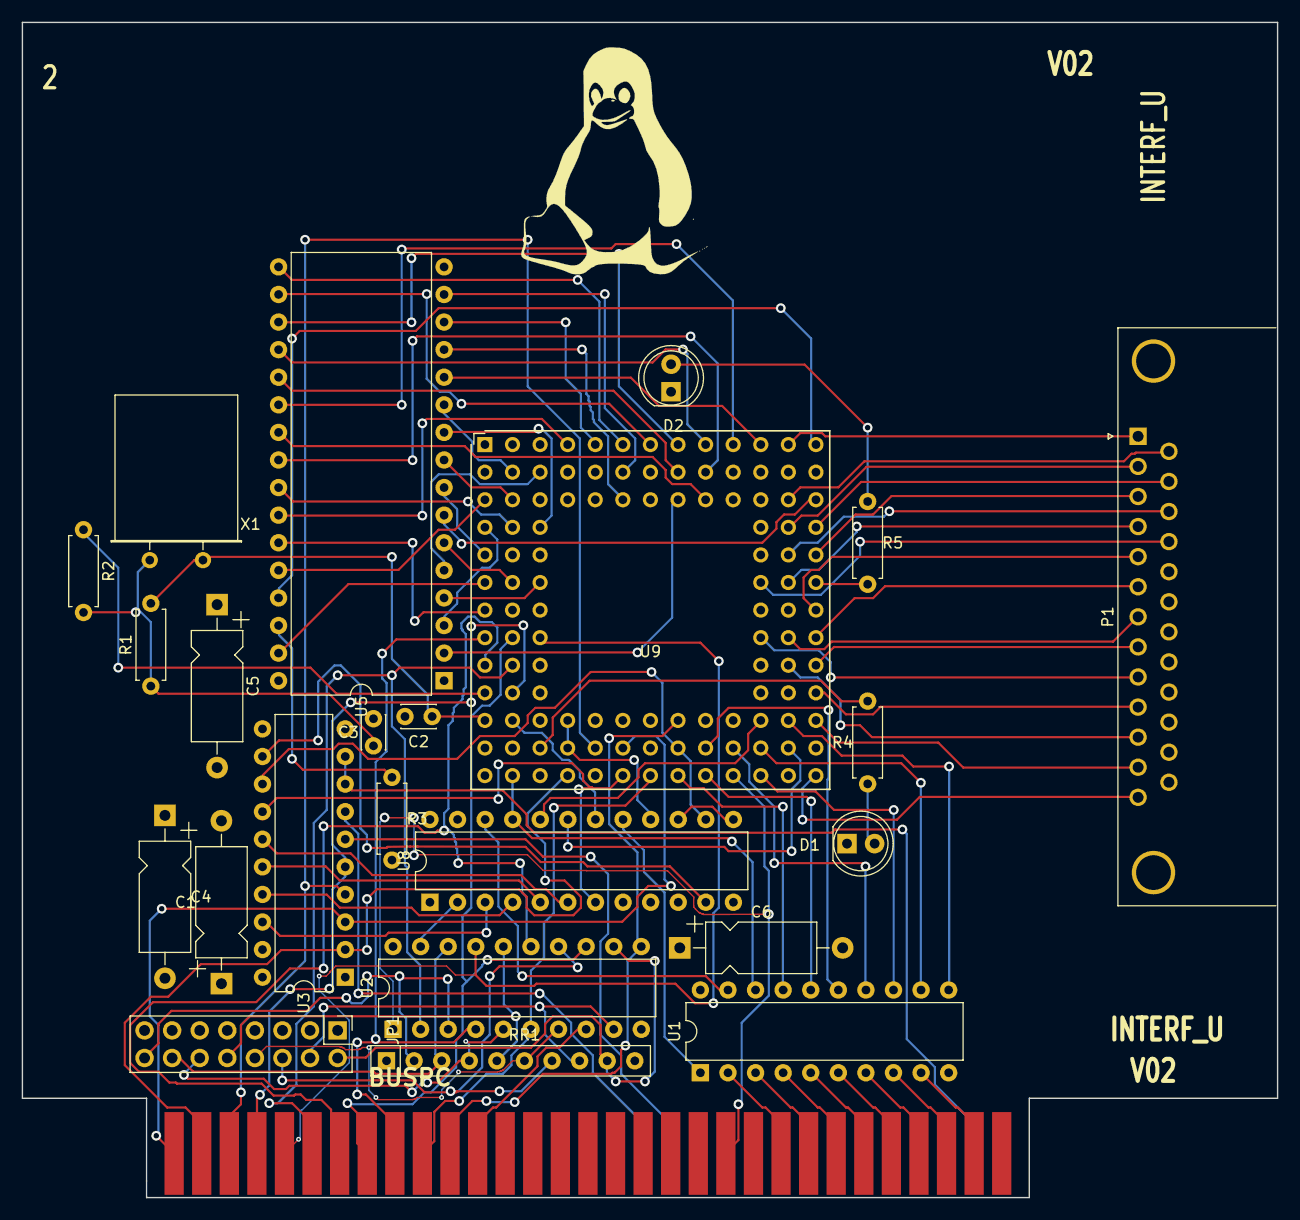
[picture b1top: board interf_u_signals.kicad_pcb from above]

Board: 2 copper layers, 115.6 x 108.2 mm, 25 parts (0 on the bottom side), 110 nets.

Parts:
BUS1: BUSPC; BUS_PC
C1, C4, C5, C6: 47uF; CP_Axial_L10.0mm_D4.5mm_P15.00mm_Horizontal
C2, C3: 47pF; C_Disc_D3.0mm_W2.0mm_P2.50mm
D1, D2: LED; LED_D5.0mm
G1: LOGO; tux
JP1: CONN_8X2; PinHeader_2x08_P2.54mm_Vertical
P1: DB25FEMELLE; DSUB-25_Female_Horizontal_P2.77x2.84mm_EdgePinOffset9.90mm_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
R1: 100K; R_Axial_DIN0207_L6.3mm_D2.5mm_P7.62mm_Horizontal
R2: 1K; R_Axial_DIN0207_L6.3mm_D2.5mm_P7.62mm_Horizontal
R3: 10K; R_Axial_DIN0207_L6.3mm_D2.5mm_P7.62mm_Horizontal
R4, R5: 330; R_Axial_DIN0207_L6.3mm_D2.5mm_P7.62mm_Horizontal
RR1: 9x1K; R_Array_SIP10
U1: 74LS245; DIP-20_W7.62mm
U2: 74LS688; DIP-20_W7.62mm
U3: 74LS541; DIP-20_W7.62mm
U5: 628128; DIP-32_W15.24mm
U8: EP600; DIP-24_W7.62mm
U9: 4003APG120; PGA120
X1: 8MHz; Crystal_HC18-U_Horizontal

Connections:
/8MH-OUT: R2.1, U9.K1 (P/A5)
/ACK: P1.10, U9.K13
/AUTOFD-: P1.14, U9.C12 (PGCK2)
/BIT0: P1.2, U9.D12
/BIT1: P1.3, U9.E13
/BIT2: P1.4, U9.F12
/BIT3: P1.5, U9.G13
/BIT4: P1.6, U9.H13
/BIT5: P1.7, U9.H12
/BIT6: P1.8, U9.J13
/BIT7: P1.9, U9.H11
/BUST+: P1.11, U9.J12
/CLKLCA: U8.16 (I/O16), U9.L4 (CCLK), U9.M4 (NC)
/CS1-: U5.22 (CS1), U9.A10
/D0: U1.18 (B0), U8.21 (I/O21), U9.N2 (DIN)
/D1: U1.17 (B1), U9.N8
/D2: U1.16 (B2), U9.N9
/D3: U1.15 (B3), U9.M9 (P/D5)
/D4: U1.14 (B4), U9.M10 (P/D6)
/D5: U1.13 (B5), U9.N11
/D6: U1.12 (B6), U9.M11 (P/D7)
/D7: U1.11 (B7), U9.L12 (SGCK3)
/DIR: U1.1 (A->B), U8.17 (I/O17)
/DONE: U8.20 (I/O20), U9.L11 (DONE)
/ENBBUF: U1.19 (CE), U8.22 (I/O22)
/ERROR-: P1.15, U9.D13
/INIT-: P1.16, U9.E12
/LED1: R4.2, U9.M3 (DOUT-SGKC4)
/LED2: R5.2, U9.F13 (INIT)
/MA0: U5.12 (A0), U9.A11
/MA1: U5.11 (A1), U9.B2 (PGCK1/A16)
/MA2: U5.10 (A2), U9.D3 (SGCK1)
/MA3: U5.9 (A3), U9.C2 (P/A14)
/MA4: U5.8 (A4), U9.E1
/MA5: U5.7 (A5), U9.C13 (LDC)
/MA6: U5.6 (A6), U9.F2
/MA7: U5.5 (A7), U9.B3 (P/A17)
/MA8: U5.27 (A8), U9.G1 (P/A8)
/MA9: U5.26 (A9), U9.A4
/MA10: U5.23 (A10), U9.C9
/MA11: U5.25 (A11), U9.D2 (P/A13)
/MA12: U5.4 (A12), U9.F3 (P/A10)
/MA13: U5.28 (A13), U9.C1 (P/A12)
/MA14: U5.3 (A14), U9.D1 (P/A11)
/MA15: U5.31 (A15), U9.F1 (P/A9)
/MA16: U5.2 (A16), U9.C8
/MATCHL: U2.19 (P=R), U8.2 (IN2)
/MD0: U5.13 (Q0), U9.C6
/MD1: U5.14 (Q1), U9.A5
/MD2: U5.15 (Q2), U9.B6
/MD3: U5.17 (Q3), U9.A6
/MD4: U5.18 (Q4), U9.A7
/MD5: U5.19 (Q5), U9.A8
/MD6: U5.20 (Q6), U9.A9
/MD7: U5.21 (Q7), U9.B8
/OE-: U5.24 (OE), U9.B9
/PC-A0: BUS1.62 (BA00), U3.3 (A1), U9.M6
/PC-A1: BUS1.61 (BA01), U3.2 (A0), U9.N4
/PC-A2: BUS1.60 (BA02), U3.4 (A2), U9.M5 (P/D1)
/PC-A3: BUS1.59 (BA03), U3.5 (A3), U9.K2 (P/CS1/A2)
/PC-A4: BUS1.58 (BA04), U2.17 (P7), U9.H3
/PC-A5: BUS1.57 (BA05), U2.2 (P0), U9.J2 (P/A4)
/PC-A6: BUS1.56 (BA06), U2.15 (P6), U9.J1
/PC-A7: BUS1.55 (BA07), U2.13 (P5), U9.H2 (P/A6)
/PC-A8: BUS1.54 (BA08), U2.4 (P1), U9.H1 (P/A7)
/PC-A9: BUS1.53 (BA09), U2.6 (P2), U9.N7 (P/D3)
/PC-A10: BUS1.52 (BA10), U2.11 (P4), U9.L8
/PC-A11: BUS1.51 (BA11), U2.8 (P3)
/PC-AEN: BUS1.42 (AEN), U2.1 (G), U9.N10 (P/CS0)
/PC-DB0: BUS1.40 (DB0), U1.2 (A0)
/PC-DB1: BUS1.39 (DB1), U1.3 (A1)
/PC-DB2: BUS1.38 (DB2), U1.4 (A2)
/PC-DB3: BUS1.37 (DB3), U1.5 (A3)
/PC-DB4: BUS1.36 (DB4), U1.6 (A4)
/PC-DB5: BUS1.35 (DB5), U1.7 (A5)
/PC-DB6: BUS1.34 (DB6), U1.8 (A6)
/PC-DB7: BUS1.33 (DB7), U1.9 (A7)
/PC-IOR: BUS1.14 (IOR), U3.7 (A5)
/PC-IOW: BUS1.13 (IOW), U3.6 (A4)
/PC-RD: U3.13 (Y5), U8.14 (IN14), U9.M8 (P/D4)
/PC-RST: BUS1.2 (RESET), U3.8 (A6), U3.9 (A7)
/PC-WR: U3.14 (Y4), U8.7 (I/O7), U9.N6 (P/RS)
/PE+: P1.12, U9.L13
/PROG-: U8.19 (I/O19), U9.M12 (PROG)
/REF4: JP1.14, RR1.3, U2.18 (R7)
/REF5: JP1.16, RR1.2, U2.3 (R0)
/REF6: JP1.10, RR1.5, U2.16 (R6)
/REF7: JP1.6, RR1.7, U2.14 (R5)
/REF8: JP1.12, RR1.4, U2.5 (R1)
/REF9: JP1.8, RR1.6, U2.7 (R2)
/REF10: JP1.2, RR1.9, U2.12 (R4)
/REF11: JP1.4, RR1.8, U2.9 (R3)
/RSTL: U3.12 (Y6), U8.11 (IN11)
/SEL_LPT: U8.18 (I/O18), U9.L2 (P/A0/WS)
/SLCT+: P1.13, U9.N13 (PGCK3)
/SLCTIN-: P1.17, U9.F11
/STROBE: P1.1, U9.A12 (SGCK2)
/WR-: U5.29 (WR), U9.A13 (HDC)
/WR_REG: U8.13 (CLK2), U8.15 (I/O15)
GND: BUS1.1 (GND), BUS1.31 (GND), C1.2, C2.2, C3.2, C4.2, C5.2, C6.2, D1.1 (K), D2.1 (K), JP1.1, JP1.3, JP1.5, JP1.7, JP1.9, JP1.11, JP1.13, JP1.15, P1.18, P1.19, P1.20, P1.21, P1.22, P1.23, P1.24, P1.25, U1.10 (GND), U2.10 (GND), U3.1 (G1), U3.10 (GND), U3.19 (G2), U5.16 (GND), U8.1 (CLK1), U8.12 (GND), U9.B7 (GND), U9.C4 (GND), U9.C10 (GND), U9.G2 (GND), U9.G11 (GND), U9.K3 (GND), U9.K11 (GND), U9.L7 (GND)
unnamed: C3.1, R1.1, R2.2, X1.2
unnamed: D1.2 (A), R4.1
unnamed: D2.2 (A), R5.1
unnamed: U3.18 (Y0), U8.3 (I/O3)
unnamed: U3.17 (Y1), U8.4 (I/O4)
unnamed: U3.16 (Y2), U8.5 (I/O5)
unnamed: U3.15 (Y3), U8.6 (I/O6)
unnamed: R3.1, U5.30 (CS2)
unnamed: C2.1, R1.2, U9.L1 (P/A3), X1.1
VCC: BUS1.3 (VCC), BUS1.29 (VCC), C1.1, C4.1, C5.1, C6.1, R3.2, RR1.1 (COM), U1.20 (VCC), U2.20 (VCC), U3.20 (VCC), U5.32 (VCC), U8.23 (IN23), U8.24 (VCC), U9.B11 (M1), U9.B12 (M2), U9.C3 (VCC), U9.C11 (M0), U9.D11 (VCC), U9.G12 (VCC), U9.L3 (VCC), U9.L10 (VCC), U9.M7 (VCC)
